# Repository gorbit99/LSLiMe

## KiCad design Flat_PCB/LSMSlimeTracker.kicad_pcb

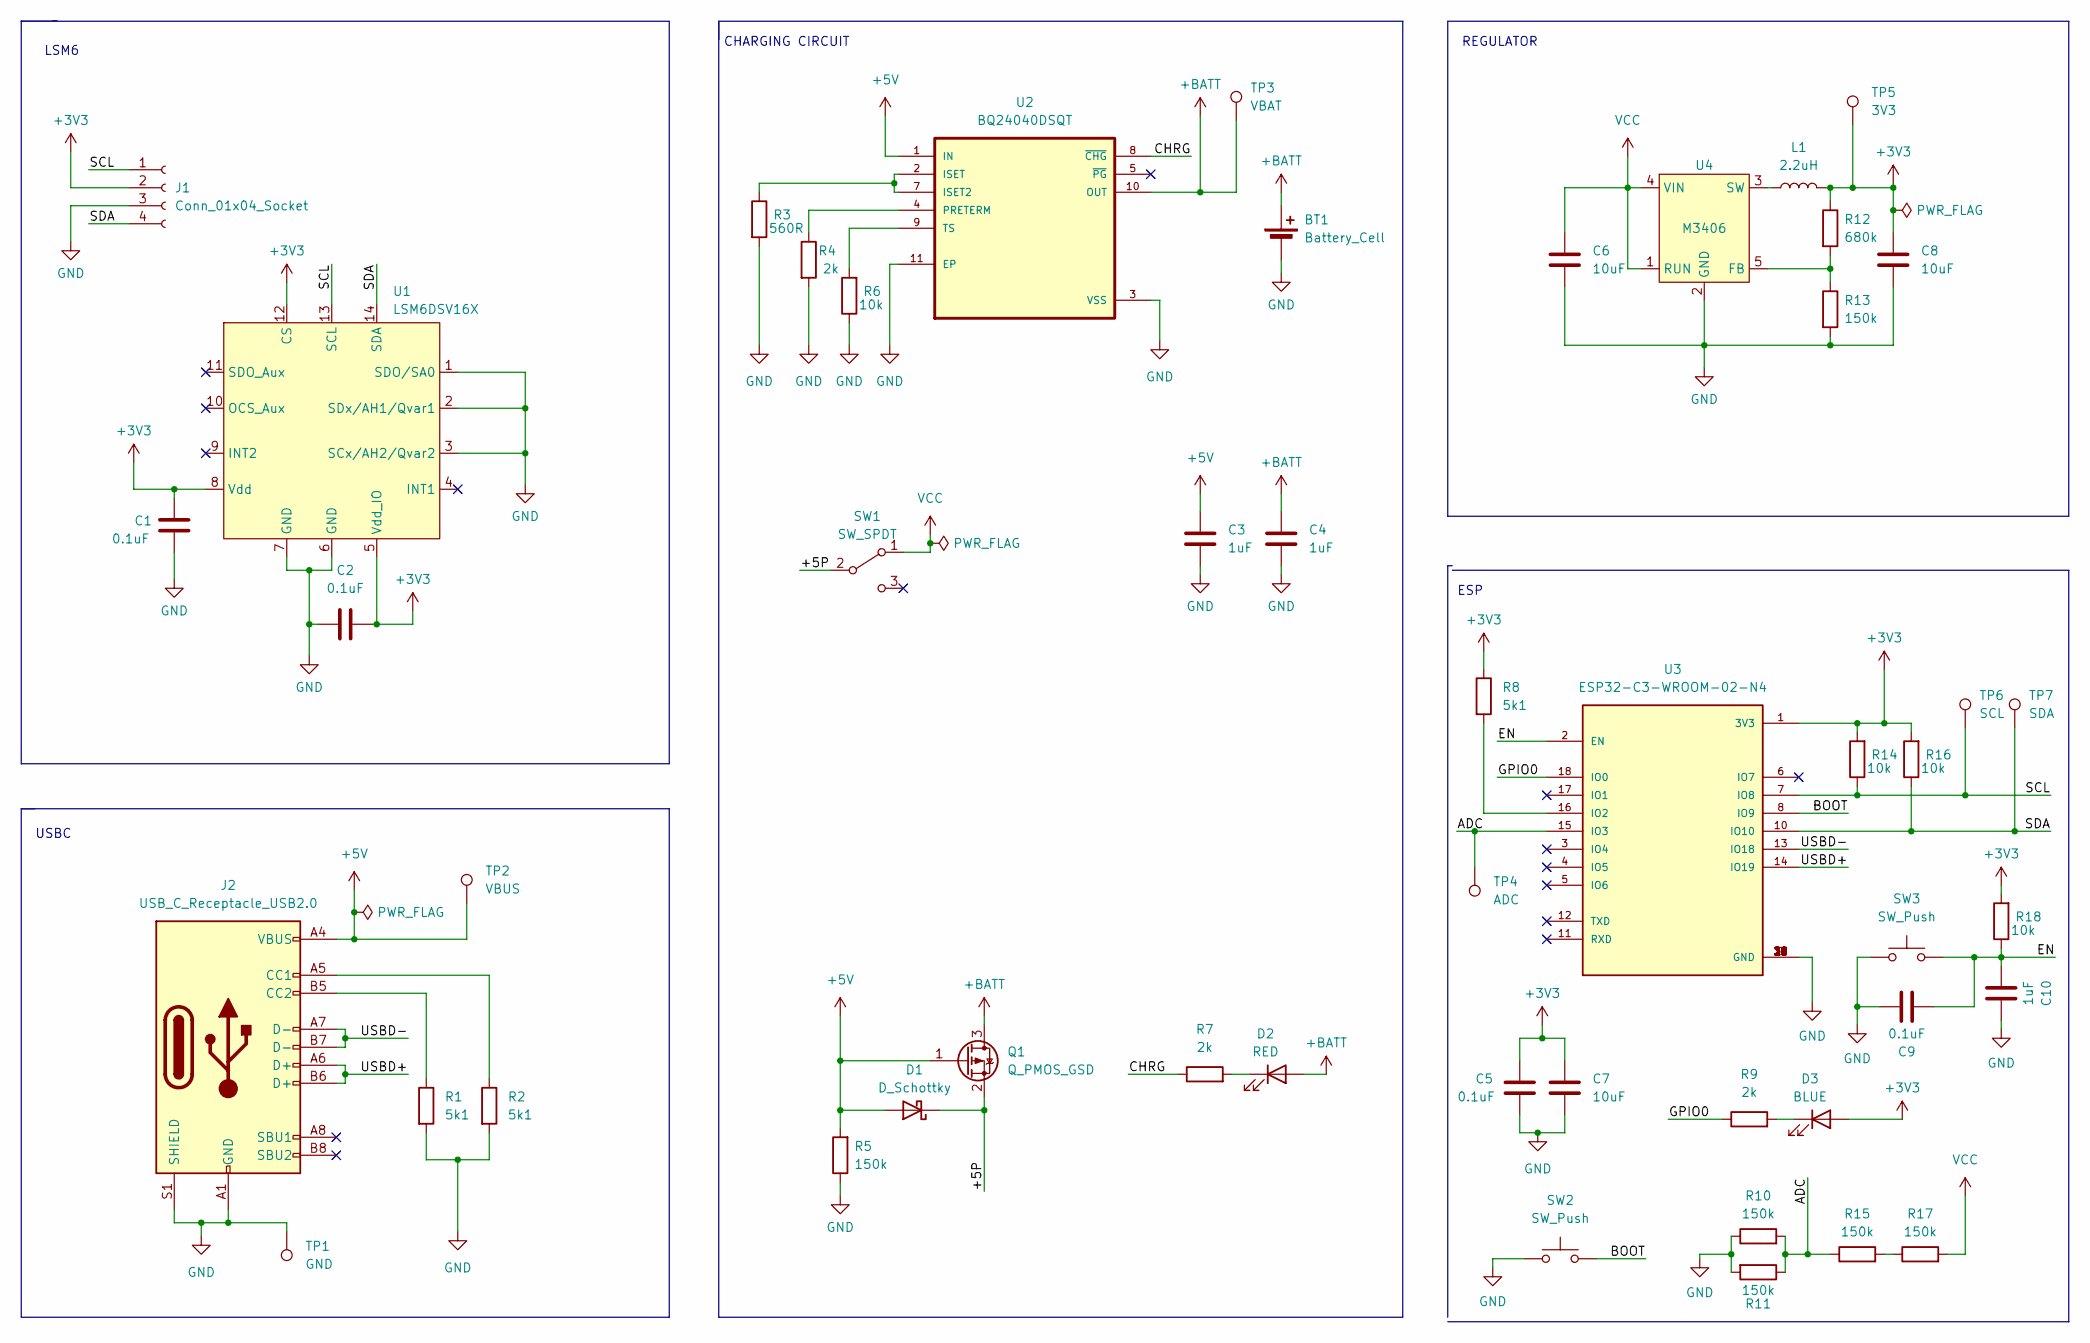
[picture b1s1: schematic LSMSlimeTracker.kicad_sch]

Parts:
BT1: Battery_Cell; JST_SH_SM02B-SRSS-TB_1x02-1MP_P1.00mm_Horizontal; MPN C189893
C1, C2: 0.1uF; C_0603_1608Metric; MPN C1525
C3, C4: 1uF; C_0603_1608Metric; MPN C52923
C5: 0.1uF; C_0603_1608Metric; MPN C52923
C6, C8: 10uF; C_0603_1608Metric; MPN C15525
C7: 10uF; C_0603_1608Metric; MPN C1525
C9: 0.1uF; C_0603_1608Metric
C10: 1uF; C_0603_1608Metric
D1: D_Schottky; D_SOD-123F; MPN C122853
D2: RED; LED_0603_1608Metric; MPN C264407
D3: BLUE; LED_0603_1608Metric; MPN C965795
J1: Conn_01x04_Socket; JST_GH_SM04B-GHS-TB_1x04-1MP_P1.25mm_Horizontal; MPN C157925
J2: USB_C_Receptacle_USB2.0; TYPE-C-31-M-12; MPN C165948
L1: 2.2uH; L_0603_1608Metric; MPN C524917
Q1: Q_PMOS_GSD; SOT-23; MPN C8549
R1, R2, R8: 5k1; R_0603_1608Metric; MPN C25905
R3: 560R; R_0603_1608Metric; MPN C103099
R4, R7, R9: 2k; R_0603_1608Metric; MPN C4109
R5, R10, R11, R13, R15, R17: 150k; R_0603_1608Metric; MPN C25755
R6, R14, R16, R18: 10k; R_0603_1608Metric; MPN C25744
R12: 680k; R_0603_1608Metric; MPN C103139
SW1: SW_SPDT; SW_SPDT_CK-JS102011SAQN; MPN C221841
SW2, SW3: SW_Push; SW_SPST_B3U-1000P
TP1: GND; TestPoint_Pad_D1.0mm
TP2: VBUS; TestPoint_Pad_D1.0mm
TP3: VBAT; TestPoint_Pad_D1.0mm
TP4: ADC; TestPoint_Pad_D1.0mm
TP5: 3V3; TestPoint_Pad_D1.0mm
TP6: SCL; TestPoint_Pad_D1.0mm
TP7: SDA; TestPoint_Pad_D1.0mm
U1: LSM6DSV16X; Bosch_LGA-14_3x2.5mm_P0.5mm; MPN C9900037528
U2: BQ24040DSQT; SON40P200X200X80-11N; MPN C2876332
U3: ESP32-C3-WROOM-02-N4; MODULE_ESP32-C3-WROOM-02-H4
U4: M3406; SOT-23-5; MPN C83224; LCSC C83224

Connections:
+3V3: C1.2, C2.2, C5.1, C7.1, C8.1, D3.2 (A), J1.2, L1.2, R8.1, R12.1, R14.2, R16.2, R18.2, TP5.1, U1.5 (Vdd_IO), U1.8 (Vdd), U1.12 (CS), U3.1 (3V3)
+5V: C3.1, D1.2 (A), J2.A4 (VBUS), J2.A9 (VBUS), J2.B4 (VBUS), J2.B9 (VBUS), Q1.1 (G), R5.2, TP2.1, U2.1 (IN)
+BATT: BT1.1 (+), C4.1, D2.2 (A), Q1.3 (D), TP3.1, U2.10 (OUT)
/+5P: D1.1 (K), Q1.2 (S), SW1.2 (B)
/ADC: R10.2, R11.1, R15.1, TP4.1, U3.15 (IO3)
/BOOT: SW2.2, U3.8 (IO9)
/CHRG: R7.1, U2.8 (~CHG)
/EN: C9.2, C10.2, R18.1, SW3.2, U3.2 (EN)
/GPIO0: R9.1, U3.18 (IO0)
/SCL: J1.1, R14.1, TP6.1, U1.13 (SCL), U3.7 (IO8)
/SDA: J1.4, R16.1, TP7.1, U1.14 (SDA), U3.10 (IO10)
/USBD+: J2.A6 (D+), J2.B6 (D+), U3.14 (IO19)
/USBD-: J2.A7 (D-), J2.B7 (D-), U3.13 (IO18)
GND: BT1.2 (-), C1.1, C2.1, C3.2, C4.2, C5.2, C6.2, C7.2, C8.2, C9.1, C10.1, J1.3, J2.A1 (GND), J2.A12 (GND), J2.B1 (GND), J2.B12 (GND), J2.S1 (SHIELD), R1.2, R2.2, R3.2, R4.2, R5.1, R6.1, R10.1, R11.2, R13.2, SW2.1, SW3.1, TP1.1, U1.1 (SDO/SA0), U1.2 (SDx/AH1/Qvar1), U1.3 (SCx/AH2/Qvar2), U1.6 (GND), U1.7 (GND), U2.3 (VSS), U2.11 (EP), U3.9 (GND), U3.19 (GND), U3.20 (GND), U3.21 (GND), U3.22 (GND), U3.23 (GND), U3.24 (GND), U3.25 (GND), U3.26 (GND), U3.27 (GND), U3.28 (GND), U3.29 (GND), U3.30 (GND), U3.31 (GND), U3.32 (GND), U3.33 (GND), U3.34 (GND), U3.35 (GND), U3.36 (GND), U3.37 (GND), U3.38 (GND), U3.39 (GND), U4.2 (GND)
unnamed: D2.1 (K), R7.2
unnamed: D3.1 (K), R9.2
unnamed: J2.A5 (CC1), R2.1
unnamed: J2.B5 (CC2), R1.1
unnamed: R15.2, R17.1
unnamed: R3.1, U2.2 (ISET), U2.7 (ISET2)
unnamed: R4.1, U2.4 (PRETERM)
unnamed: R6.2, U2.9 (TS)
unnamed: R8.2, U3.16 (IO2)
unnamed: R12.2, R13.1, U4.5 (FB)
unnamed: L1.1, U4.3 (SW)
VCC: C6.1, R17.2, SW1.1 (A), U4.1 (RUN), U4.4 (VIN)

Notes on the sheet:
LSM6
REGULATOR
CHARGING CIRCUIT
USBC
ESP

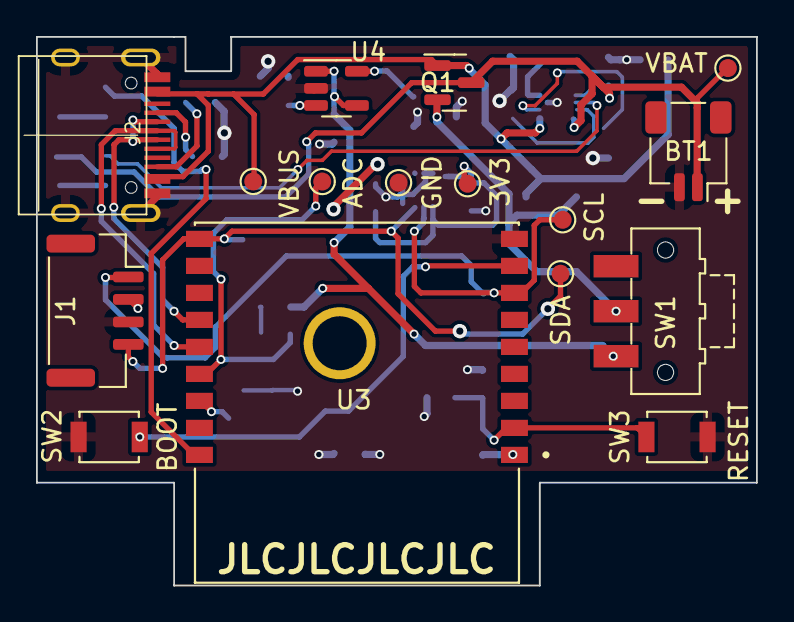
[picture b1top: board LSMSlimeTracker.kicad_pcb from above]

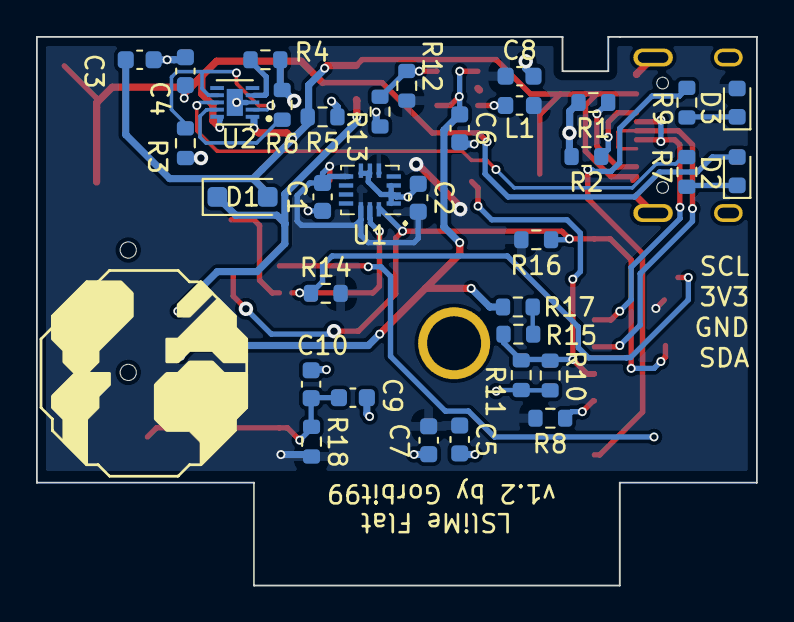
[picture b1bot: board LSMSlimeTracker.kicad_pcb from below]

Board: 2 copper layers, 40.0 x 30.5 mm, 50 parts (34 on the bottom side), 26 nets.

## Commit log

2023-07-31 Initial
2023-07-31 TTDM fix
2023-07-31 Moved USB C to top
2023-08-01 Updated pdf
2023-09-06 V1.2
